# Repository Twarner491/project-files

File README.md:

# Welcome to My Project Files Repo!

Here I publish each iteration of my project files, along with any dependent files/tools/libraries - check out this repo's history to see file progression.

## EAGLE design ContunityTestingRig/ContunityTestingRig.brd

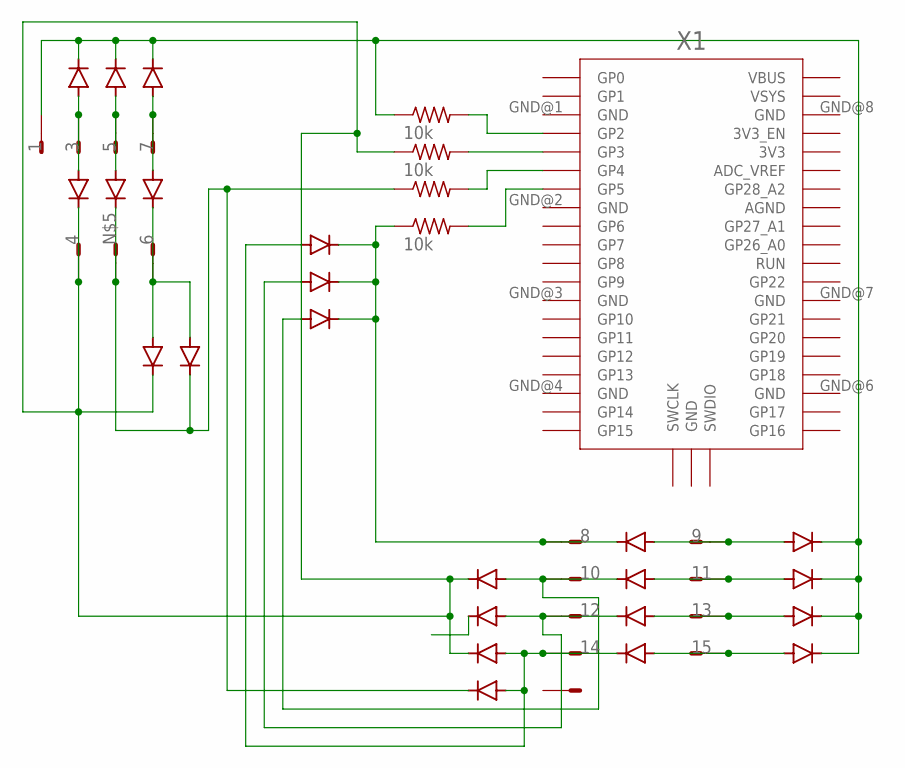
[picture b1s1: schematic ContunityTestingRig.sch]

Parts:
D1, D2, D3, D4, D5, D6, D7, D8, D9, D10, D11, D12, D13, D14, D15, D16, D17, D18, D19, D20, D21, D22, D23: SCHOTTKY; MINI-SMA
R1, R2, R3, R4: 10k; R1206FAB
SV1: 16E; 16P
X1: RPI_PICO_IG-SMD; RPI_PICO

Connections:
1: D1.KATHODE, D2.KATHODE, D3.KATHODE, D13.KATHODE, D14.KATHODE, D15.KATHODE, D16.KATHODE, R1.1, SV1.1
3: D1.ANODE, D4.ANODE, SV1.3
4: D4.KATHODE, D7.KATHODE, D17.KATHODE, D18.KATHODE, R2.1, SV1.2
5: D2.ANODE, D5.ANODE, SV1.5
6: D6.KATHODE, D7.ANODE, D8.ANODE, SV1.6
7: D3.ANODE, D6.ANODE, SV1.7
8: D9.KATHODE, D21.KATHODE, D22.KATHODE, D23.KATHODE, R4.1, SV1.8
9: D9.ANODE, D13.ANODE, SV1.9
10: D10.KATHODE, D17.ANODE, D23.ANODE, SV1.10
11: D10.ANODE, D14.ANODE, SV1.11
12: D11.KATHODE, D19.ANODE, D22.ANODE, SV1.12
13: D11.ANODE, D15.ANODE, SV1.13
14: D12.KATHODE, D18.ANODE, D20.ANODE, D21.ANODE, SV1.14
15: D12.ANODE, D16.ANODE, SV1.15
unnamed: R1.2, X1.GP2
unnamed: R2.2, X1.GP3
unnamed: R3.2, X1.GP4
unnamed: R4.2, X1.GP5
unnamed: D5.KATHODE, D8.KATHODE, D20.KATHODE, R3.1, SV1.4

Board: 2 copper layers, 29 parts (0 on the bottom side), 19 nets, no tracks yet.

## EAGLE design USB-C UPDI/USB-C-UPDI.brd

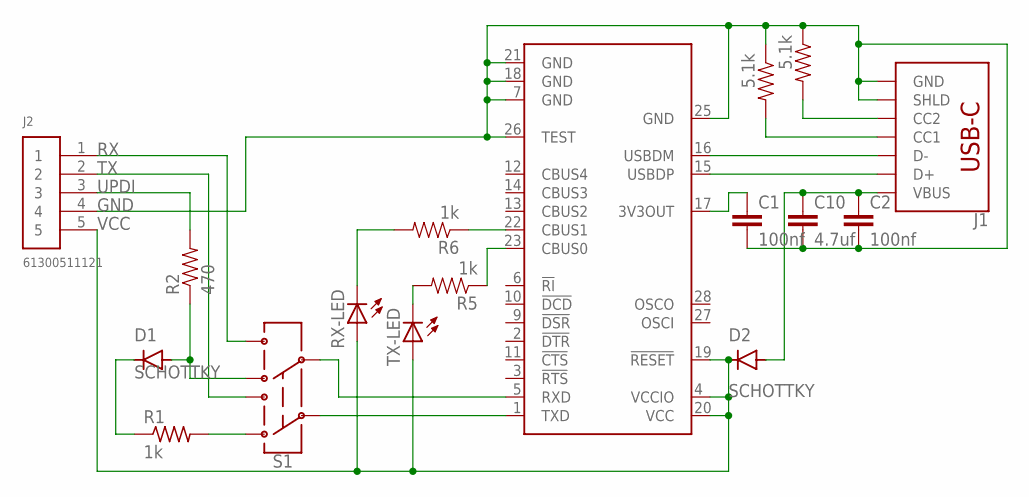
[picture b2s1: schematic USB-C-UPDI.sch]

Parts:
C1, C2: 100nf; 1206
C10: 4.7uf; 1206
D1, D2: SCHOTTKY; MINI-SMA
IC1: FT232RL; SSOP28
J1: USB_C_4-LAYER_PADS; USB-C-16P_4LAYER-PADS
J2: 61300511121
R1: 1k; R1206FAB
R2: 470; 1206
R5, R6: 1k; 1206
R9, R10: 5.1k; 1206
RX-LED: LED; LED1206
S1: SWITCH-DPDT-SMD-AYZ0202; SWITCH_DPDT_SMD_AYZ0202
TX-LED: LED; LED1206

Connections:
GND: C1.2, C2.2, C10.2, IC1.7 (GND), IC1.18 (GND), IC1.21 (GND), IC1.25 (GND), IC1.26 (TEST), J1.GND, J1.GND2 (GND), J1.SHLD1 (SHLD), J1.SHLD2 (SHLD), J1.SHLD3 (SHLD), J1.SHLD4 (SHLD), J2.4, R9.1, R10.1
unnamed: C1.1, IC1.17 (3V3OUT)
unnamed: IC1.16 (USBDM), J1.A7 (D-), J1.B7 (D-)
unnamed: D1.ANODE, R2.1, S1.6
unnamed: D1.KATHODE, R1.1
unnamed: IC1.15 (USBDP), J1.A6 (D+), J1.B6 (D+)
unnamed: IC1.5 (RXD), S1.5
unnamed: J1.A5 (CC1), R9.2
unnamed: IC1.1 (TXD), S1.2
unnamed: R1.2, S1.3
unnamed: J1.B5 (CC2), R10.2
unnamed: IC1.22 (CBUS1), R6.1
unnamed: IC1.23 (CBUS0), R5.1
unnamed: R5.2, TX-LED.2 (C)
unnamed: R6.2, RX-LED.2 (C)
unnamed: C2.1, C10.1, D2.ANODE, J1.VBUS1 (VBUS), J1.VBUS2 (VBUS)
RX: J2.1, S1.4
TX: J2.2, S1.1
UPDI: J2.3, R2.2
VCC: D2.KATHODE, IC1.4 (VCCIO), IC1.19 (!RESET), IC1.20 (VCC), J2.5, RX-LED.1 (A), TX-LED.1 (A)

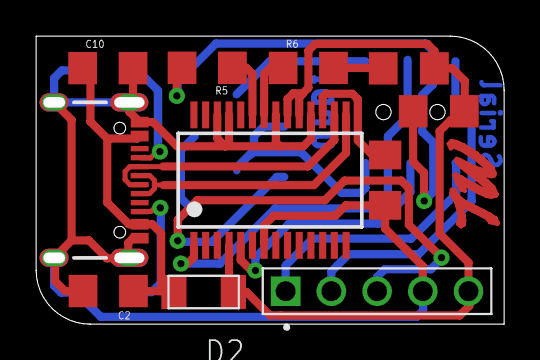
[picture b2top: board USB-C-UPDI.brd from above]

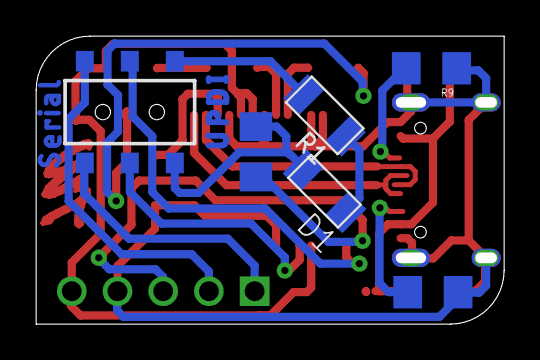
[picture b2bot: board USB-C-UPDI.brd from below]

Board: 2 copper layers, 25.4 x 15.4 mm, 17 parts (6 on the bottom side), 20 nets.

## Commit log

2021-06-19 Marlin Push
2021-09-15 readme updates
2021-09-15 sticker folder
2021-09-15 Stikers
2021-09-17 profile updates
2021-09-21 generator upload
2021-10-17 stencil
2021-10-17 Stencil Update
2021-10-24 ftid2updi
2021-10-24 ftdi2updi Updates
2021-10-24 ftdi2updu meshing update
2021-10-27 via updates
2021-11-06 gerber files
2021-11-17 UPDI updates
2021-12-08 solar cell push
2022-02-02 logo updates
2022-02-25 programmer updates
2022-02-26 USB-C UPDI Updates
2022-04-02 topography update
2022-05-17 jig upload
2022-08-24 SET Logos
2022-08-30 3D Print
2022-08-31 Test Print Removeal
2022-09-20 Arduino Case File Upload
2022-10-07 Contunity Testing Rig
2022-10-08 file structure updates
2022-10-08 file fix
2022-10-08 workspace update
2022-10-22 Code Workspace Update

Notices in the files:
parts and their libraries:
01_SparkFun: Licensing: CC v3.0 Share-Alike You are welcome to use this library for commercial purposes.
SparkFun-Connectors: Licensing: Creative Commons ShareAlike 4.0 International - https://creativecommons.org/licenses/by-sa/4.0
